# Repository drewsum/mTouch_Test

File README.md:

# mTouch_Test
Small PCB for playing around with PIC mTouch capacitive touch methods and USB serial ports

Firmware for U201 written in MPLABX, built using microchip's XC8 compiler

8/12/2018: PCB has been ordered via OSHPark

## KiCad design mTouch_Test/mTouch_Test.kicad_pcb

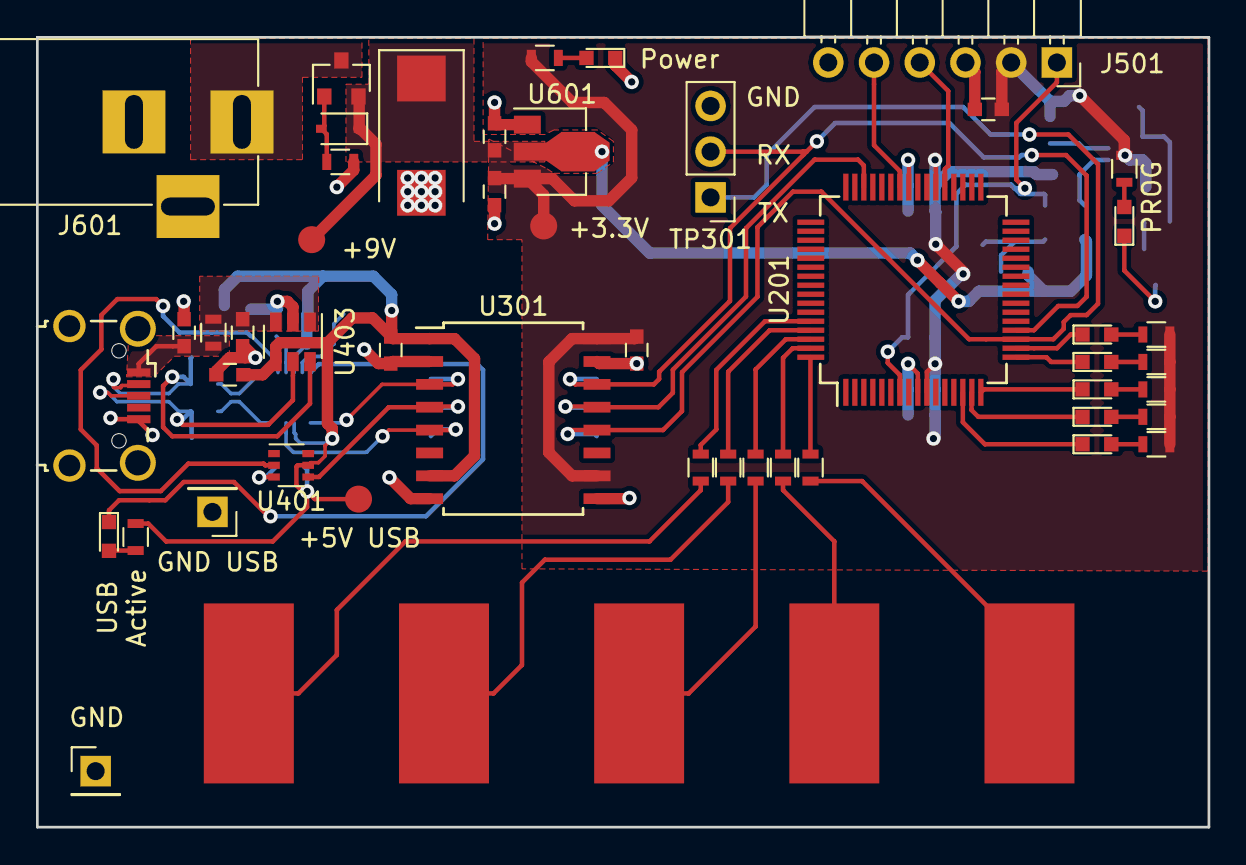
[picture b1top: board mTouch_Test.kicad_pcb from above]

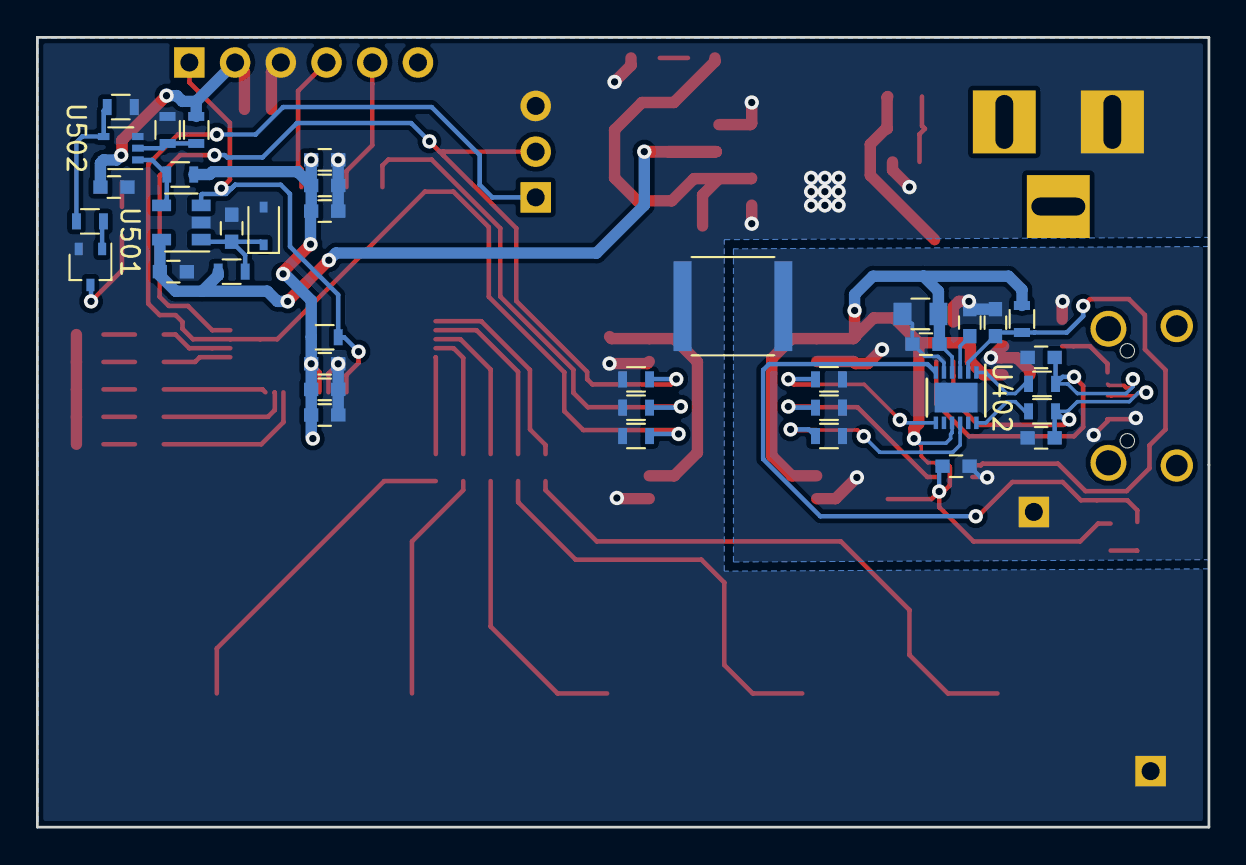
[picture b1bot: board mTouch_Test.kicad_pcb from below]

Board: 2 copper layers, 65.1 x 43.9 mm, 91 parts (38 on the bottom side), 54 nets.

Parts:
C201, C204, C301, C303, C401, C402, C404, C406, C408, C409, C410, C501, C502, C503, C504: 0.1uF; C_0603
C202, C205: 10nF; C_0603
C203, C206: 1nF; C_0603
C302: 56000pF; C_2220
C403: 4.7uF; C_0805
C405, C407: 47pF; C_0603
C601: 100uF; CP_Tantalum_Case-X_EIA-7343-43_Reflow
C602, C603: 1uF; C_0603
D201, D202, D203, D204, D205, D501: Red; LED_0603
D401: Yellow; LED_0603
D601: Green; LED_0603
J401: USB_B_Micro; USB_Micro-B_Wuerth-629105150521_CircularHoles
J501: Prog; PICKIT3_Header
J601: Barrel_Jack_Switch; BARREL_JACK
L401: 600R 0.5A; L_0603
Q501: BSS214NW; SOT-323_SC-70
Q601: Si2319CDS; SOT-23
R201, R301, R302, R303, R304, R305, R306, R401, R501, R502, R503, R505, R601: 10k; R_0603
R202, R203, R204, R205, R206: 220; R_0603
R207, R208, R209, R210, R211, R404, R507, R602: 1k; R_0603
R402, R403: 27; R_0603
R504: 0; R_0603
R506: 10; R_0603
TP201, TP202, TP203, TP204, TP205: TP; SolderWirePad_single_SMD_5x10mm
TP301: UART; Pin_Header_Straight_1x03_Pitch2.54mm
TP401, TP602, TP603: TP; Measurement_Point_Round-SMD-Pad_Small
TP402, TP601: TP; Pin_Header_Straight_1x01_Pitch2.54mm
U201: PIC18LF67K40-I_PT; TQFP-64_10x10mm_Pitch0.5mm
U301: ISO7331C; SOIC-16W_7.5x10.3mm_Pitch1.27mm
U401: 74LVC1G17; SOT-363_SC-70-6
U402: FT234XD; DFN-12-1EP_3x3mm_Pitch0.45mm
U403: TPD3S014DBVR; SOT-23-6
U501: TL331; SOT-23-5
U502: 74LVC1G86; SOT-353_SC-70-5
U601: MCP1700-3302E; SOT-89-3
Z501, Z601: BZT52C5V6S; D_SOD-323

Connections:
+3V3: C201.1, C202.1, C203.1, C204.1, C205.1, C206.1, C301.1, C503.1, C504.1, C603.1, J501.2, R201.1, R207.1, R208.1, R209.1, R210.1, R211.1, R502.1, R503.1, R507.1, R602.1, TP603.1, U201.10, U201.38, U301.10, U301.16, U502.5, U601.3
+5V_USB: C303.1, C402.1, C403.1, C406.1, C410.1, R401.1, R404.1, TP401.1, U301.1, U301.7, U401.5, U402.4, U402.9, U403.4
+9V: C502.1, C601.1, C602.1, Q601.2, R501.1, TP602.1, U501.5, U601.2, Z601.1
/USB_UART_Converter/BRIDGE_USB+: R402.1, U402.12
/USB_UART_Converter/BRIDGE_USB-: R403.2, U402.1
/USB_UART_Converter/CONN_USB+: C405.1, J401.3, R402.2, U403.5
/USB_UART_Converter/CONN_USB-: C407.1, J401.2, R403.1, U403.6
GND: C201.2, C202.2, C203.2, C204.2, C205.2, C206.2, C301.2, C302.2, C501.2, C502.2, C503.2, C504.2, C601.2, C602.2, C603.2, D601.1, J501.3, J601.2, Q501.2, R301.2, R302.2, R303.2, R504.2, R505.2, R601.2, TP301.3, TP601.1, U201.9, U201.41, U301.9, U301.15, U501.2, U502.3, U601.1, Z501.2
GND_USB: C302.1, C303.2, C401.2, C402.2, C403.2, C404.2, C405.2, C406.2, C407.2, C408.2, C409.2, C410.2, J401.5, R304.2, R305.2, R306.2, TP402.1, U301.2, U301.8, U401.3, U402.5, U402.13, U403.2
ICSPCLK: J501.5, U201.42
ICSPDAT: J501.4, U201.37
ICSP_DETECT: R505.1, R506.2, U502.4
unnamed: C401.1, R401.2, U401.2, U402.2
unnamed: C404.1, U402.3
unnamed: C408.1, L401.2, U403.1, U403.3
unnamed: C409.1, J401.1, L401.1
unnamed: C501.1, R501.2, U501.1, Z501.1
unnamed: D201.2, R207.2
unnamed: D202.2, R208.2
unnamed: D203.2, R209.2
unnamed: D204.2, R210.2
unnamed: D205.2, R211.2
unnamed: D401.2, R404.2
unnamed: D501.1, Q501.3
unnamed: D501.2, R507.2
unnamed: D601.2, R602.2
unnamed: J601.1, Q601.3
unnamed: Q501.1, R506.1
unnamed: Q601.1, R601.1, Z601.2
unnamed: R202.1, U201.64
unnamed: R202.2, TP201.1
unnamed: R203.1, U201.63
unnamed: R203.2, TP202.1
unnamed: R204.1, U201.62
unnamed: R204.2, TP203.1
unnamed: R205.1, U201.61
unnamed: R205.2, TP204.1
unnamed: R206.1, U201.60
unnamed: R206.2, TP205.1
unnamed: R502.2, U501.4, U502.1
unnamed: R503.2, R504.1, U502.2
USB_DTR: R301.1, U201.46, U301.13
USB_DTR_ISO: R306.1, U301.4, U401.4
USB_UART_RX: R303.1, TP301.2, U201.20, U301.14
USB_UART_RX_ISO: R304.1, U301.3, U402.7
USB_UART_TX: R302.1, TP301.1, U201.19, U301.12
USB_UART_TX_ISO: R305.1, U301.5, U402.10
~LED1: D201.1, U201.18
~LED2: D202.1, U201.17
~LED3: D203.1, U201.16
~LED4: D204.1, U201.15
~LED5: D205.1, U201.14
~MCLR: J501.1, R201.2, U201.7, U501.3
~USB_ACTIVE: D401.1, U402.6

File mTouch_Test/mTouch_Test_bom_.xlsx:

Component | References | Value | Quantity Per PCB | Datasheet | Digi-Key PN | display_footprint | Dielectric | Voltage | Tolerance | Wattage
1 | C201 C204 C301 C303 C401 C402 C404 C406 C408 C409 C410 C501 C502 C503 C504 | 0.1uF | 15 |  | 399-6856-1-ND | 603 | X7R | 50V
2 | C601 | 100uF | 1 |  | 718-1031-1-ND | 7343 |  | 20V | 0.1
3 | C202 C205 | 10nF | 2 |  | 490-4781-1-ND | 603 | X7R | 50V
4 | C203 C206 | 1nF | 2 |  | 399-3293-1-ND | 603 | X7R | 50V
5 | C602 C603 | 1uF | 2 |  | 478-5010-1-ND | 603 | X7R | 16V
6 | C403 | 4.7uF | 1 |  | 445-6969-1-ND | 805 | X7R | 16V
7 | C405 C407 | 47pF | 2 |  | 478-3692-1-ND | 603 | X7R | 50V
8 | C302 | 56000pF | 1 |  | 490-7747-1-ND | 2220 | X7R | 250VAC
9 | D601 | Green | 1 |  | 511-1308-1-ND | 603
10 | D201 D202 D203 D204 D205 D501 | Red | 6 |  | 511-1310-1-ND | 603
11 | D401 | Yellow | 1 |  | 511-1305-1-ND | 603
12 | J601 | Barrel_Jack_Switch | 1 | ~ | SC237-ND
13 | J501 | Prog | 1
14 | J401 | USB_B_Micro | 1 | ~ | 732-5960-1-ND
15 | L401 | 600R 0.5A | 1 | ~ | 732-1593-1-ND
16 | Q501 | BSS214NW | 1 | https://www.infineon.com/dgdl/Infineon-BSS214NW-DS-v02_02-en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 | BSS214NWH6327XTSA1CT-ND
17 | Q601 | Si2319CDS | 1 | http://www.vishay.com/docs/66709/si2319cd.pdf | SI2319CDS-T1-GE3CT-ND
18 | R504 | 0 | 1 |  | P0.0GCT-ND | 603 |  |  | 0.01 | 1/10W
19 | R506 | 10 | 1 |  | 311-10.0HRCT-ND | 603 |  |  | 0.01 | 1/10W
20 | R201 R301 R302 R303 R304 R305 R306 R401 R501 R502 R503 R505 R601 | 10k | 13 |  | RHM10KADCT-ND | 603 |  |  | 0.01 | 1/10W
21 | R207 R208 R209 R210 R211 R404 R507 R602 | 1k | 8 |  | YAG2323CT-ND | 603 |  |  | 0.01 | 1/10W
22 | R202 R203 R204 R205 R206 | 220 | 5 |  | RHM220DCT-ND | 603 |  |  | 0.01 | 1/10W
23 | R402 R403 | 27 | 2 |  | P27.0HCT-ND | 603 |  |  | 0.01 | 1/10W
24 | U401 | 74LVC1G17 | 1 | http://www.ti.com/lit/sg/scyt129e/scyt129e.pdf | 296-16998-1-ND
25 | U502 | 74LVC1G86 | 1 | http://www.ti.com/lit/sg/scyt129e/scyt129e.pdf | 296-9854-1-ND
26 | U402 | FT234XD | 1 | http://www.ftdichip.com/Support/Documents/DataSheets/ICs/DS_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 | 768-1178-1-ND
27 | U301 | ISO7331C | 1 | http://www.ti.com/lit/ds/symlink/iso7331c.pdf | 296-47261-1-ND
28 | U601 | MCP1700-3302E | 1 | http://ww1.microchip.com/downloads/en/DeviceDoc/20001826C.pdf | MCP1700T3302EMBCT-ND
29 | U201 | PIC18LF67K40-I_PT | 1 |  | PIC18LF67K40T-I/PTCT-ND
30 | U501 | TL331 | 1 | http://www.ti.com/lit/ds/symlink/tl331.pdf | 296-10168-1-ND
31 | U403 | TPD3S014DBVR | 1 | http://www.ti.com/lit/ds/symlink/tpd3s014.pdf | 296-38835-1-ND
32 | Z501 Z601 | BZT52C5V6S | 2 |  | BZT52C5V6S-TPMSCT-ND | SOD323 |  | 5.6V
Component Groups:
Component Count:
Fitted Components:
Number of PCBs:
Total components:
Schematic Version:
Schematic Date:
BoM Date:
Schematic Source:
KiCad Version:

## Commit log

2018-08-11 Imported a few schematic sheets from VFD_Clock project
2018-08-11 Added programming sheet, replaced a lot of messed up symbols
2018-08-12 Finished schematic, assigned DigiKey PNs
2018-08-12 Assigned PCB footprints, generated netlist
2018-08-12 Added PDF
2018-08-12 USB circuits arranged
2018-08-12 Arranged micro
2018-08-12 Arranged programing detection circuits
2018-08-12 Finished fisrt pass of arranging parts
2018-08-12 Added board edge
2018-08-12 Routed a considerable portion of the board
2018-08-12 Finished Routing
2018-08-12 Added Bill of Materials
2018-08-28 Changed +9V Net to +5V due to errors in LDO input voltage constraints
2018-08-28 Added firmware project for U201 firmware
2018-08-28 Added ring buffer interface APIs, imported from an earlier project. Altered all EUSART variable references and macros to match EUSART2 as this module is used for USB debug communication
2018-08-28 Edited ring buffer interface LUT to match certain parameters of the circuit design
2018-08-28 Added IDN SCPI command to supported serial commands, removed LED blinking test
2018-08-28 Added MCC generated mTouch files
2018-08-28 Added button press functionality into main loop
2018-08-28 Added functionality to interface mTouch buttons with serial debug
2018-08-28 Edited reset message
2018-08-28 Added USB DTR interrupt functionality, and changed eusart ready flag from uint8_t to bit data type
2018-08-29 Added note about compiling sfw in README.md
2018-09-02 Rewrote a lot of code, got the firmware to the point I want it
